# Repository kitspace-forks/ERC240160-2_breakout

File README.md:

# ERC240160-2 Breakout

A quick breakout board for the 3.4" 240x160 Graphic LCD COG with Touch, available from here: https://www.buydisplay.com/3-4-inch-graphic-touch-screen-lcd-cog-display-240x160-single-sided-fpc

Datasheet: https://www.buydisplay.com/download/manual/ERC240160-2_Series_Datasheet.pdf

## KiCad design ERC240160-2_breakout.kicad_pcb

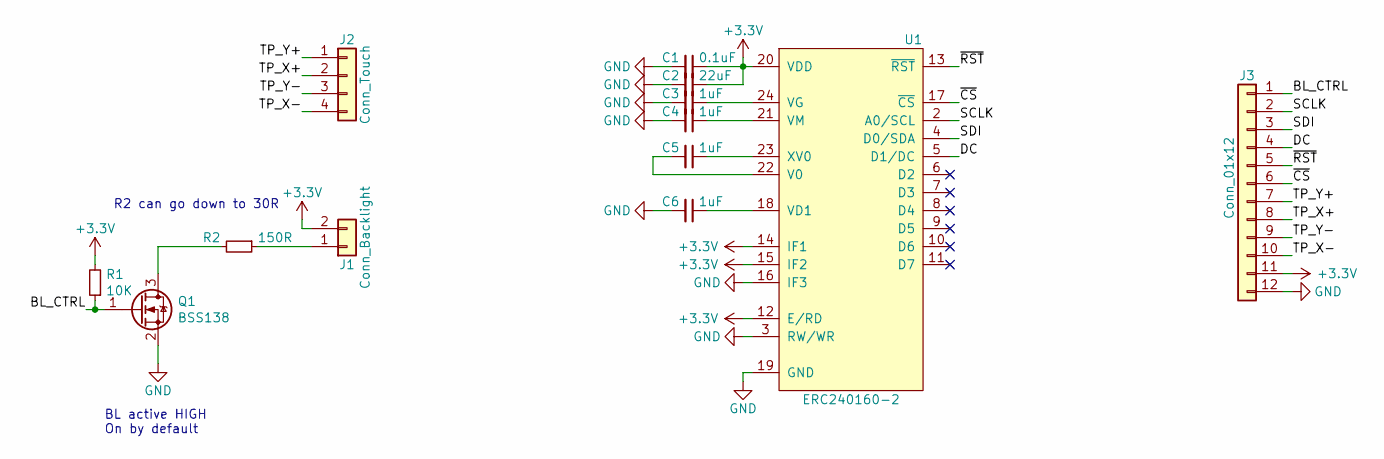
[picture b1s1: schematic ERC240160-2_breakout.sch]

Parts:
C1: 0.1uF; C_0603_1608Metric
C2: 22uF; C_0603_1608Metric
C3, C4, C5, C6: 1uF; C_0603_1608Metric
J1: Conn_Backlight; JST_PH_S2B-PH-SM4-TB_1x02-1MP_P2.00mm_Horizontal
J2: Conn_Touch; Molex_200528-0040_1x04-1MP_P1.00mm_Horizontal
J3: Conn_01x12; PinHeader_1x12_P2.54mm_Vertical
Q1: BSS138; SOT-23
R1: 10K; R_0603_1608Metric
R2: 150R; R_0603_1608Metric
U1: ERC240160-2; Hirose_FH12-25S-0.5SH_1x25-1MP_P0.50mm_Horizontal

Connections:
+3V3: C1.1, C2.1, J1.2, J3.11, R1.2, U1.12 (E/RD), U1.14 (IF1), U1.15 (IF2), U1.20 (VDD)
/BL_CTRL: J3.1, Q1.1 (G), R1.1
/DC: J3.4, U1.5 (D1/DC)
/SCLK: J3.2, U1.2 (A0/SCL)
/SDI: J3.3, U1.4 (D0/SDA)
/TP_X+: J2.2, J3.8
/TP_X-: J2.4, J3.10
/TP_Y+: J2.1, J3.7
/TP_Y-: J2.3, J3.9
/~CS~: J3.6, U1.17 (~CS~)
/~RST~: J3.5, U1.13 (~RST~)
GND: C1.2, C2.2, C3.2, C4.2, C6.2, J3.12, Q1.2 (S), U1.1 (ESD), U1.3 (RW/WR), U1.16 (IF3), U1.19 (GND), U1.25 (ESD)
unnamed: C3.1, U1.24 (VG)
unnamed: C4.1, U1.21 (VM)
unnamed: C5.1, U1.23 (XV0)
unnamed: C5.2, U1.22 (V0)
unnamed: C6.1, U1.18 (VD1)
unnamed: J1.1, R2.1
unnamed: Q1.3 (D), R2.2

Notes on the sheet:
BL active HIGH On by default
R2 can go down to 30R

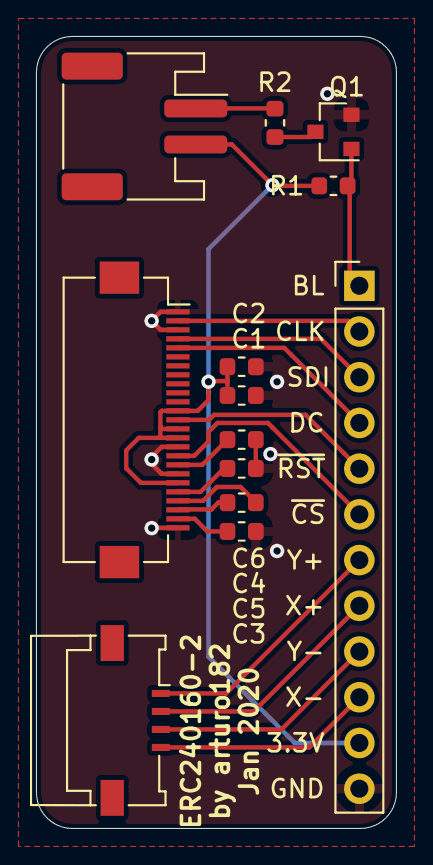
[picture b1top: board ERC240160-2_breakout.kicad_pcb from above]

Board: 2 copper layers, 20.0 x 44.0 mm, 13 parts (0 on the bottom side), 19 nets.

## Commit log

2020-01-14 Rev 1
2020-01-14 Add kitspace.yaml
